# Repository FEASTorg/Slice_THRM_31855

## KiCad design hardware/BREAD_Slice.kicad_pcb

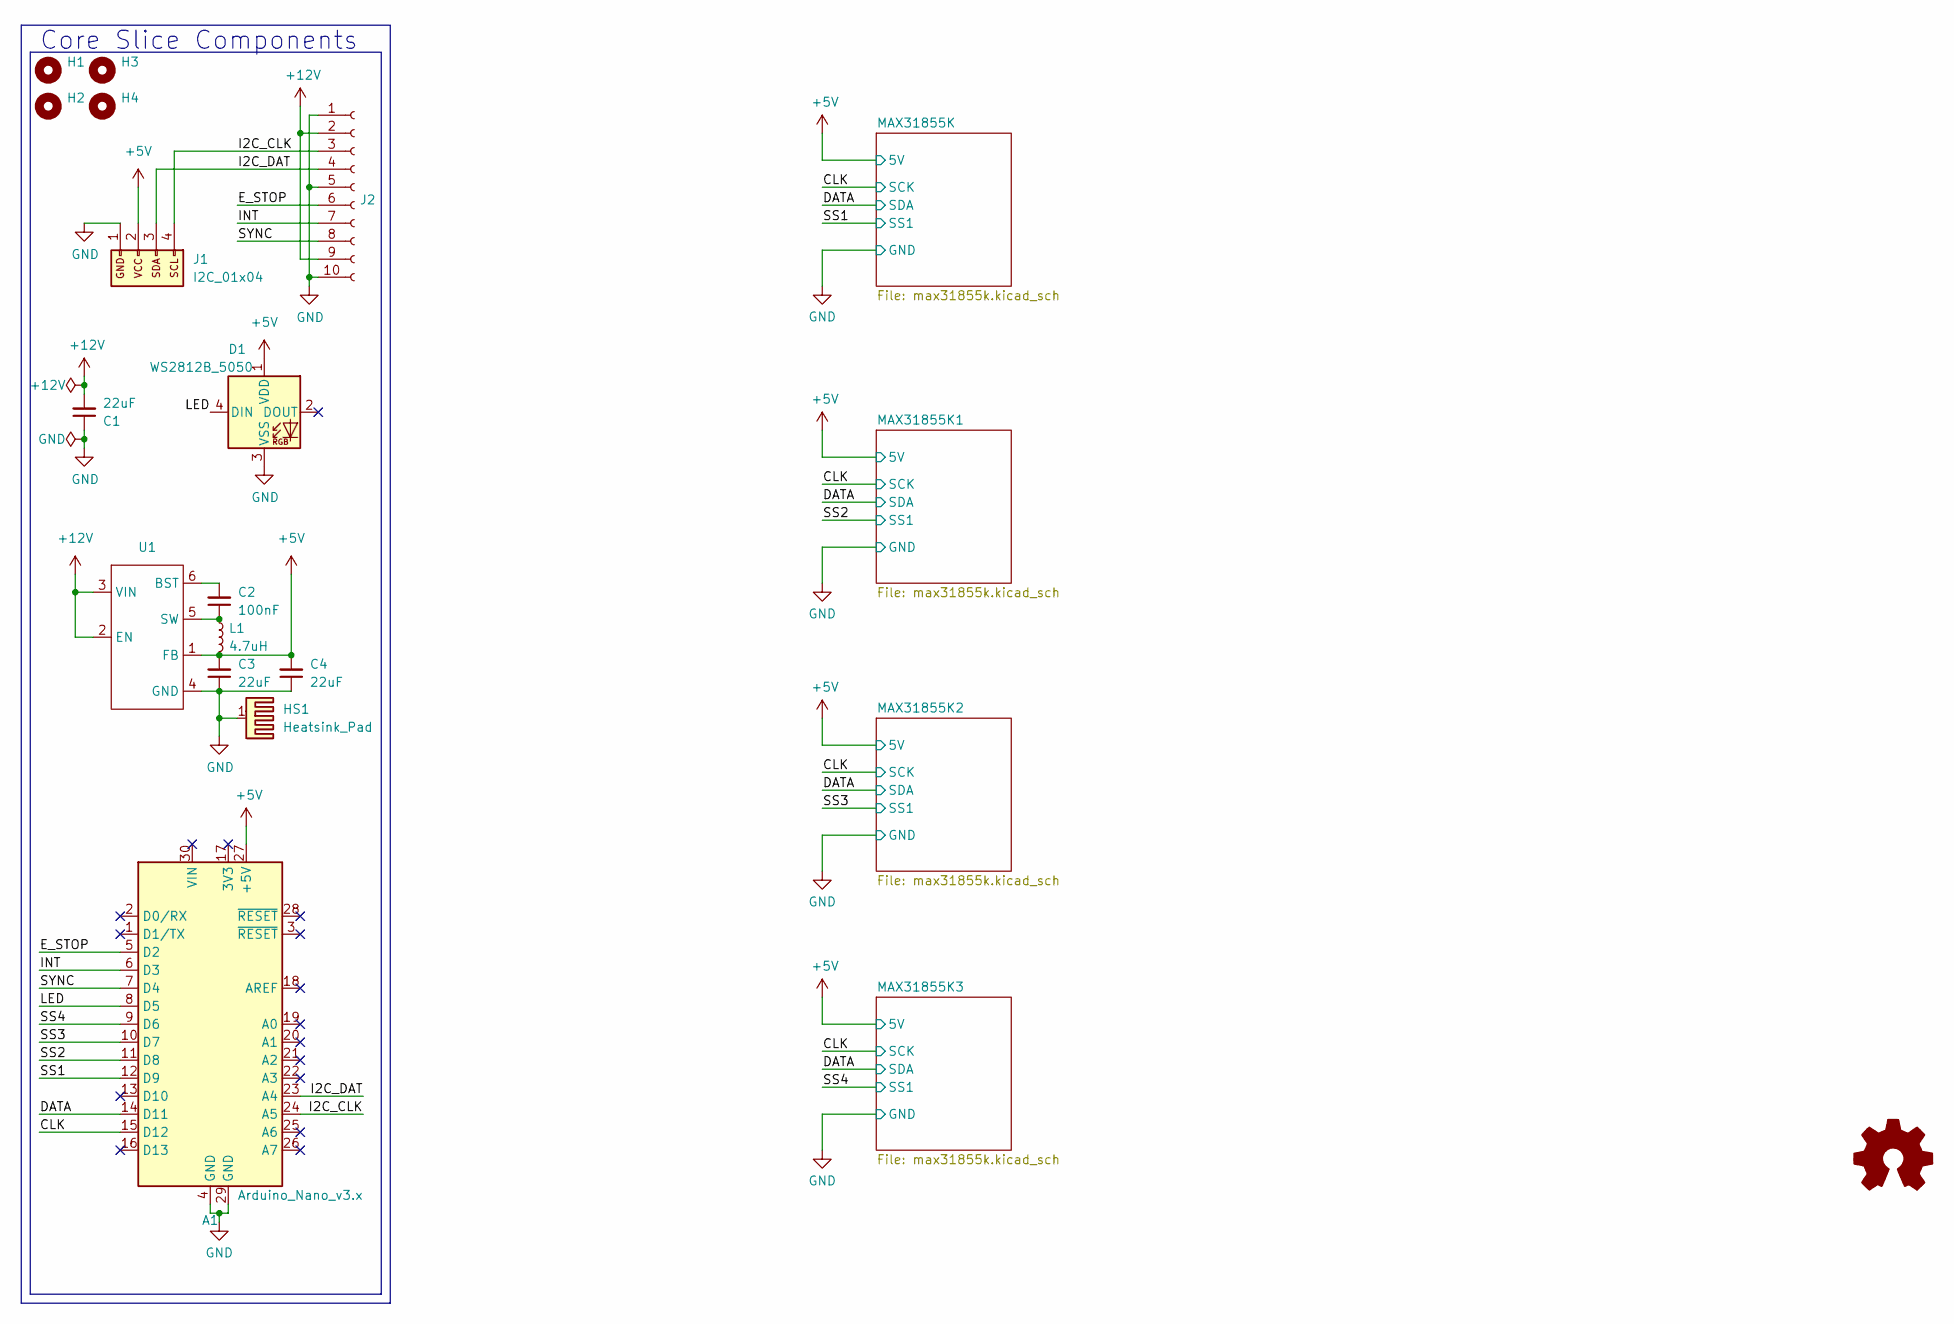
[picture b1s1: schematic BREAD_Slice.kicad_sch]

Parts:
A1: Arduino_Nano_v3.x; Arduino_Nano
C1, C3, C4: 22uF; C_1206_3216Metric
C2: 100nF; C_1206_3216Metric
D1: WS2812B_5050; WS2812-5050-4PIN
H1, H2, H3, H4: MountingHole; MountingHole_5mm
HS1: Heatsink_Pad; Thermal Pad
J1: I2C_01x04; JST_SH_SM04B-SRSS-TB_1x04-1MP_P1.00mm_Horizontal
J2: Conn_01x10_Female; PinSocket_1x10_P2.54mm_Horizontal
L1: 4.7uH; L_1210_3225Metric
U1: TSOT-23-6

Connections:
+5V: A1.27 (+5V), C3.2, C4.2, D1.1 (VDD), J1.2, L1.2, U1.1 (FB); also elsewhere on the board
+12V: C1.2, J2.2, J2.9, U1.2 (EN), U1.3 (VIN)
/CLK: A1.15 (D12); also elsewhere on the board
/DATA: A1.14 (D11); also elsewhere on the board
/E_STOP: A1.5 (D2), J2.6
/I2C_CLK: A1.24 (A5), J1.4, J2.3
/I2C_DAT: A1.23 (A4), J1.3, J2.4
/INT: A1.6 (D3), J2.7
/LED: A1.8 (D5), D1.4 (DIN)
/SS1: A1.12 (D9); also elsewhere on the board
/SS2: A1.11 (D8); also elsewhere on the board
/SS3: A1.10 (D7); also elsewhere on the board
/SS4: A1.9 (D6); also elsewhere on the board
/SYNC: A1.7 (D4), J2.8
GND: A1.4 (GND), A1.29 (GND), C1.1, C3.1, C4.1, D1.3 (VSS), HS1.1, J1.1, J2.1, J2.5, J2.10, U1.4 (GND); also elsewhere on the board
unnamed: C2.2, U1.6 (BST)
unnamed: C2.1, L1.1, U1.5 (SW)

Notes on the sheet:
Core Slice Components

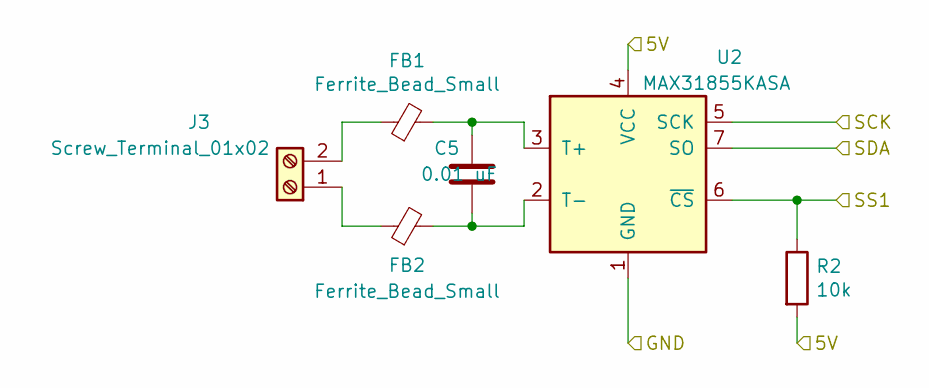
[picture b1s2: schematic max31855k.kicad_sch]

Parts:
C5: 0.01 uF; C_1206_3216Metric_Pad1.33x1.80mm_HandSolder
FB1, FB2: Ferrite_Bead_Small; R_1206_3216Metric_Pad1.30x1.75mm_HandSolder
J3: Screw_Terminal_01x02; TerminalBlock_TE_282834-2_1x02_P2.54mm_Horizontal
R2: 10k; R_1206_3216Metric_Pad1.30x1.75mm_HandSolder
U2: MAX31855KASA; SOIC-8_3.9x4.9mm_P1.27mm

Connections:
+5V: R2.2, U2.4 (VCC); also elsewhere on the board
/CLK: U2.5 (SCK); also elsewhere on the board
/DATA: U2.7 (SO); also elsewhere on the board
/SS1: R2.1, U2.6 (~CS); also elsewhere on the board
GND: U2.1 (GND); also elsewhere on the board
unnamed: FB2.1, J3.1
unnamed: FB1.1, J3.2
unnamed: C5.1, FB1.2, U2.3 (T+)
unnamed: C5.2, FB2.2, U2.2 (T-)

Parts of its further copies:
C6, C7, C8: 0.01 uF; C_1206_3216Metric_Pad1.33x1.80mm_HandSolder
FB3, FB4, FB5, FB6, FB7, FB8: Ferrite_Bead_Small; R_1206_3216Metric_Pad1.30x1.75mm_HandSolder
J4, J5, J6: Screw_Terminal_01x02; TerminalBlock_TE_282834-2_1x02_P2.54mm_Horizontal
R3, R4, R5: 10k; R_1206_3216Metric_Pad1.30x1.75mm_HandSolder
U3, U4, U5: MAX31855KASA; SOIC-8_3.9x4.9mm_P1.27mm

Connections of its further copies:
+5V: R3.2, R4.2, R5.2, U3.4 (VCC), U4.4 (VCC), U5.4 (VCC); also elsewhere on the board
/CLK: U3.5 (SCK), U4.5 (SCK), U5.5 (SCK); also elsewhere on the board
/DATA: U3.7 (SO), U4.7 (SO), U5.7 (SO); also elsewhere on the board
/SS2: R3.1, U3.6 (~CS); also elsewhere on the board
/SS3: R4.1, U4.6 (~CS); also elsewhere on the board
/SS4: R5.1, U5.6 (~CS); also elsewhere on the board
GND: U3.1 (GND), U4.1 (GND), U5.1 (GND); also elsewhere on the board
unnamed: FB4.1, J4.1
unnamed: FB3.1, J4.2
unnamed: FB6.1, J5.1
unnamed: FB5.1, J5.2
unnamed: FB8.1, J6.1
unnamed: FB7.1, J6.2
unnamed: C6.1, FB3.2, U3.3 (T+)
unnamed: C6.2, FB4.2, U3.2 (T-)
unnamed: C7.1, FB5.2, U4.3 (T+)
unnamed: C7.2, FB6.2, U4.2 (T-)
unnamed: C8.1, FB7.2, U5.3 (T+)
unnamed: C8.2, FB8.2, U5.2 (T-)

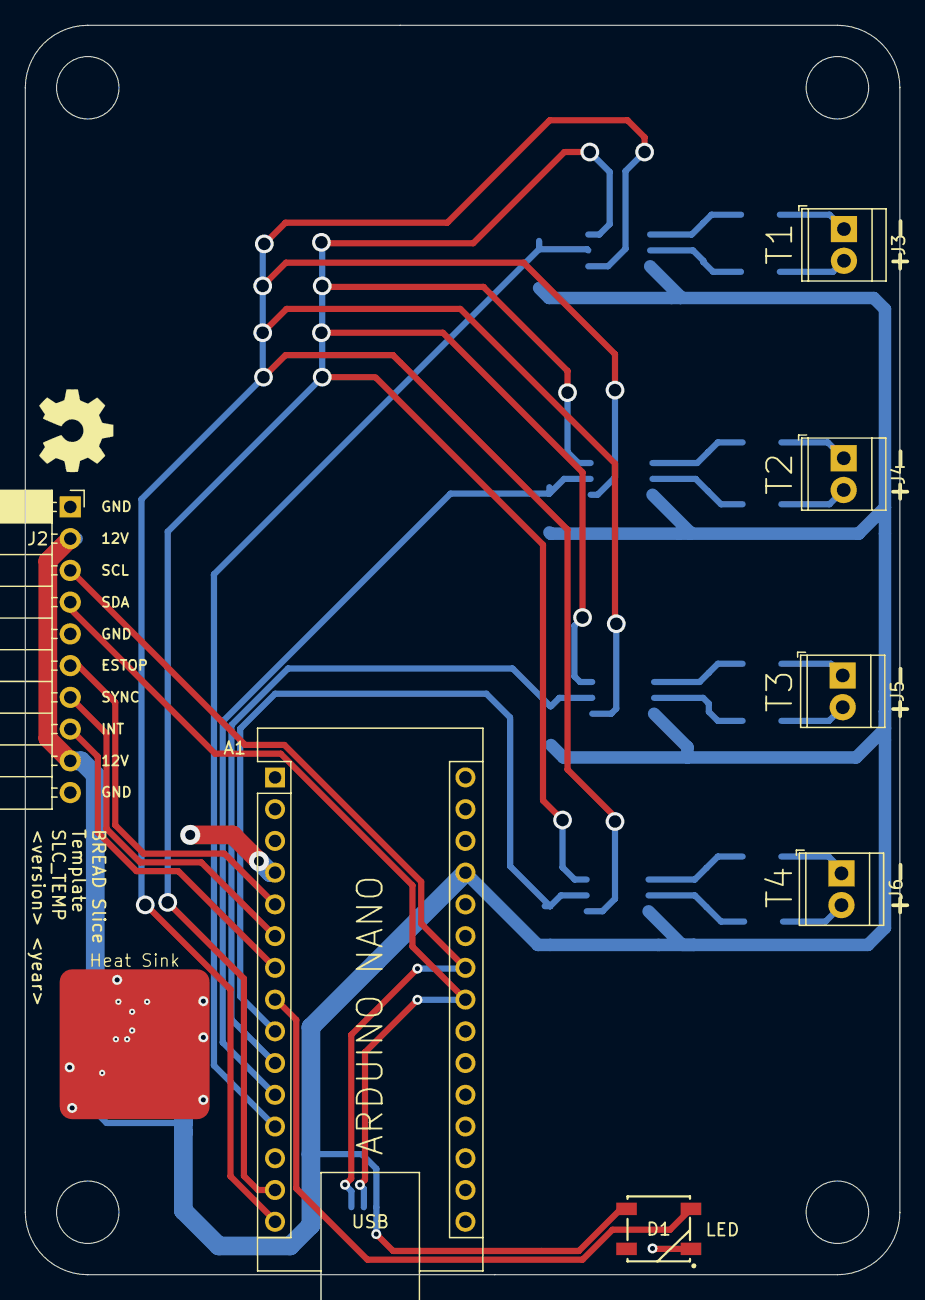
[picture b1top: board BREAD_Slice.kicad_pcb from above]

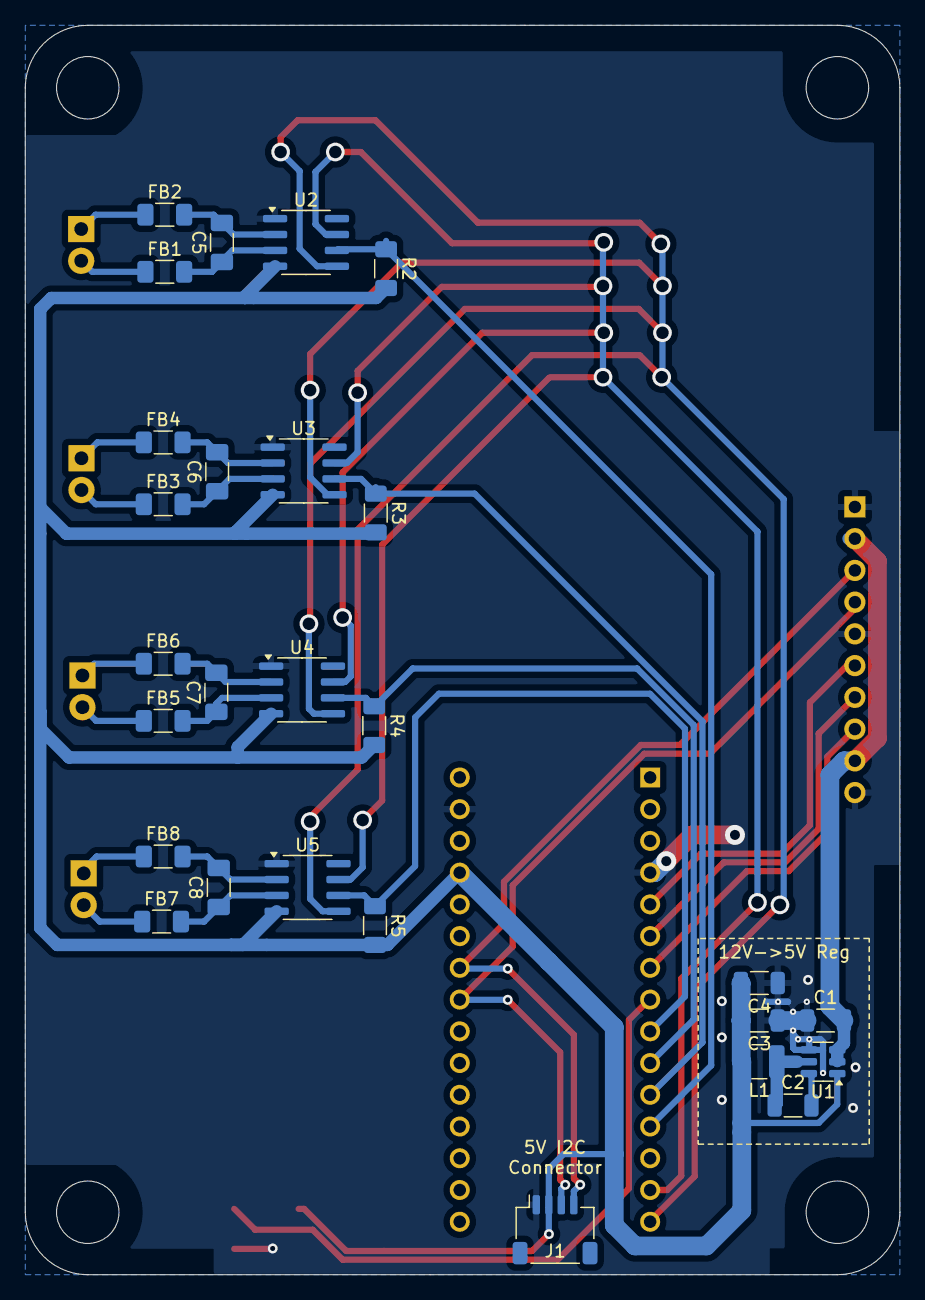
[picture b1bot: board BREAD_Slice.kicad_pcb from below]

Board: 2 copper layers, 70.0 x 100.0 mm, 40 parts (27 on the bottom side), 33 nets.

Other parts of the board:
Logo1: Logo_Open_Hardware_Small; OSHW-Symbol_6.7x6mm_SilkScreen

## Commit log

2025-09-25 initial commit after split
2025-09-25 hw: save schem to KiCad9 and add pwr flags to clear erc
2025-09-25 ci: add bread-infra pipeline and all docs template files
2025-09-25 hw ci: add missing kibot files
2025-09-25 📄 KiBot index + board renders (auto)
